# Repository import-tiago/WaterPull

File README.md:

# Water Pull
WaterPull is an electronic polymer dryer focused on removing moisture from 3D printer filaments. It has control and adjustment of temperature and curing time, internal air circulation and alarms.

## PCB Preview

## Enclosure Preview

## Schematic

### Contributing
0. Give this project a :star:
1. Create an issue and describe your idea.
2. [Fork it](https://github.com/import-tiago/WaterPull/fork).
3. Create your feature branch (`git checkout -b my-new-feature`).
4. Commit your changes (`git commit -a -m "Added feature title"`).
5. Publish the branch (`git push origin my-new-feature`).
6. Create a new pull request.
7. Done! :heavy_check_mark:

### License Information
<br /><span xmlns:dct="http://purl.org/dc/terms/" property="dct:title">ChristmasTree</span> by <a xmlns:cc="http://creativecommons.org/ns#" href="https://github.com/import-tiago" property="cc:attributionName" rel="cc:attributionURL">Tiago Silva</a> is licensed under a <a rel="license" href="http://creativecommons.org/licenses/by-sa/4.0/">Creative Commons Attribution-ShareAlike 4.0 International License</a>.<br />Permissions beyond the scope of this license may be available at <a xmlns:cc="http://creativecommons.org/ns#" href="https://twitter.com/import_tiago" rel="cc:morePermissions">tiagodepaulasilva@gmail.com</a>.

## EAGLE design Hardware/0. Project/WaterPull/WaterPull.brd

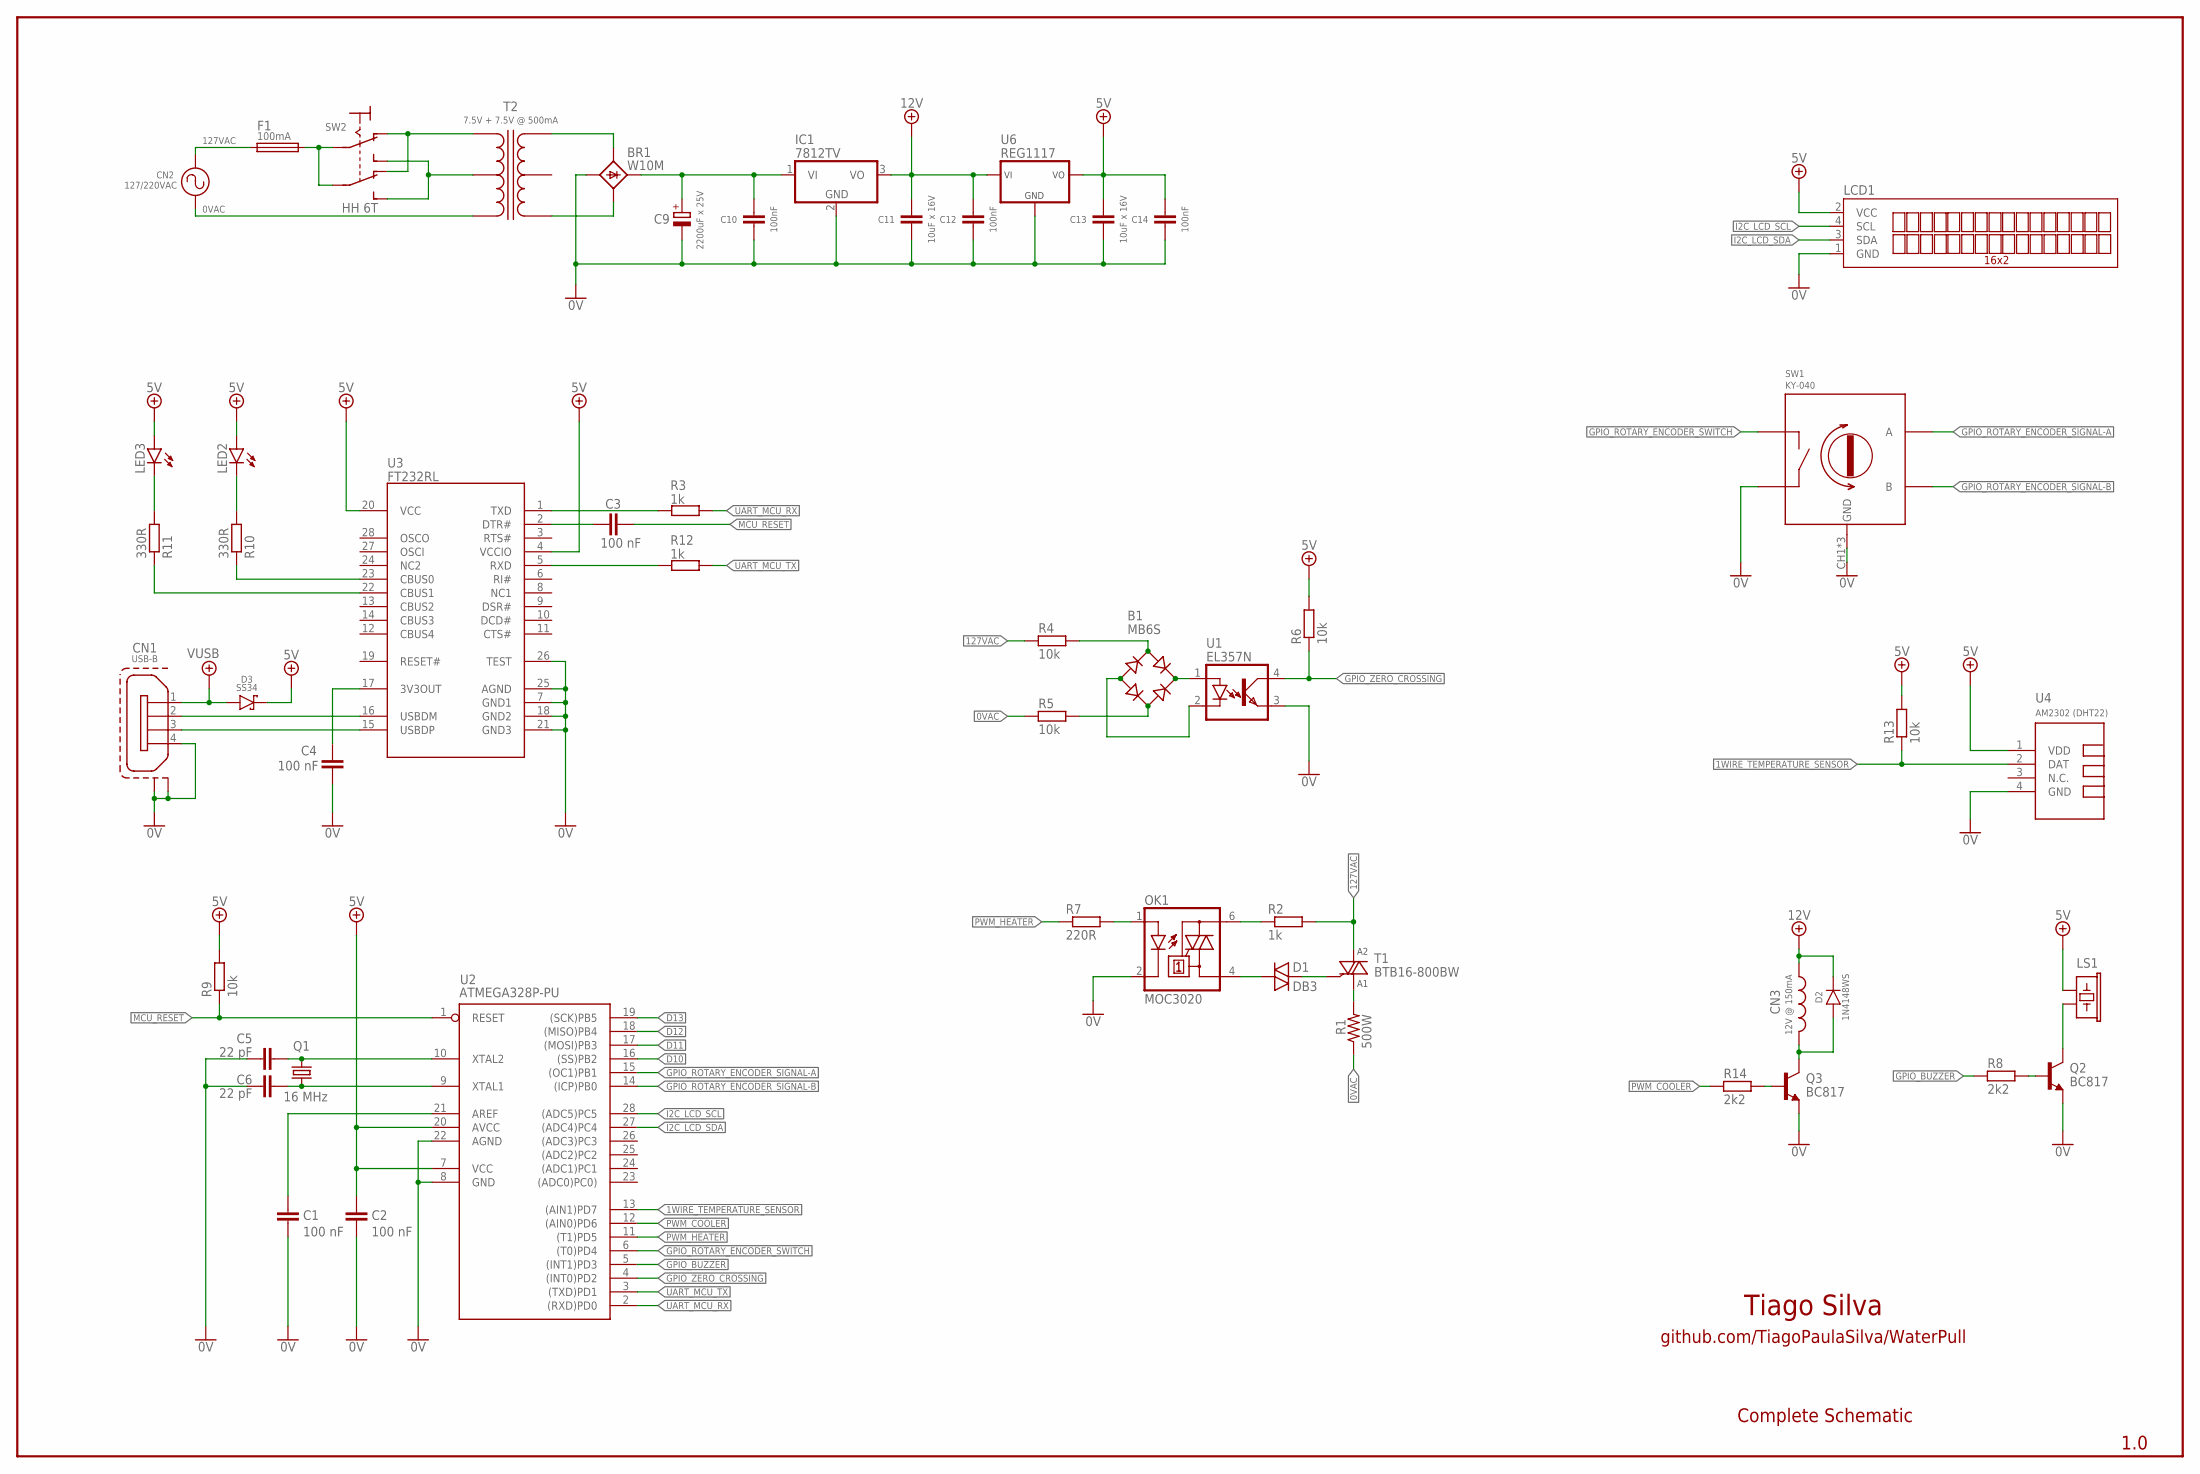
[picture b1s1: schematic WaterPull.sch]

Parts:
B1: MB6S; SOIC-4
BR1: W10M; DIOB_W005M
C1, C2, C3, C4: 100 nF; C0805
C5, C6: 22 pF; C0805
C9: 2200uF x 25V; E7,5-16
C10, C12, C14: 100nF; C0805
C11, C13: 10uF x 16V; C0805
CN1: USB-B
CN2: 127/220VAC; AK500/2-H
CN3: 12V @ 150mA; JST-PH2
D1: DB3; DO35-10
D2: 1N4148WS; SOD323F
D3: SS34; DO214AB
IC1: 7812TV; TO220V
LCD1: TUXGR_16X2_R2
LED2, LED3: LEDCHIPLED_0805; CHIPLED_0805
LS1: BUZZER-PTH; BUZZER-12MM
OK1: MOC3020; DIL06
Q1: 16 MHz; HC49/S
Q2, Q3: BC817; SOT23-BEC
R1: 500W; AK500/2-H
R2: 1k; 0207/7
R3, R12: 1k; R0805
R4, R5: 10k; 0207/7
R6, R9, R13: 10k; R0805
R7: 220R; R0805
R8, R14: 2k2; R0805
R10, R11: 330R; R0805
SW1: KY-040
T1: BTB16-800BW; TO220BH
T2: 7.5V + 7.5V @ 500mA; 3PINS
U1: EL357N; SOP254P700X200-4N
U2: ATMEGA328P-PU; DIL28-3
U3: FT232RL; SSOP28
U4: AM2302 (DHT22); TEMP-HUM-SENSOR-DHT22
U6: REG1117; SOT223

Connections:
0V: BR1.-, C1.2, C2.2, C4.1, C5.1, C6.1, C9.-, C10.2, C11.2, C12.2, C13.2, C14.2, CN1.4, CN1.M1 (S1), CN1.M2 (S2), IC1.2 (GND), LCD1.1 (GND), OK1.2 (C), Q2.E, Q3.E, SW1.CH1 (GND), SW1.CH2 (GND), SW1.GND, SW1.SW2, U1.3 (E), U2.8 (GND), U2.22 (AGND), U3.7 (GND1), U3.18 (GND2), U3.21 (GND3), U3.25 (AGND), U3.26 (TEST), U4.4 (GND), U6.1 (GND)
0VAC: CN2.1, R1.1, R5.1
1WIRE_TEMPERATURE_SENSOR: R13.1, U2.13 ((AIN1)PD7), U4.2 (DAT)
5V: C2.1, C13.1, C14.1, D3.C (K), LCD1.2 (VCC), LED2.A, LED3.A, LS1.+ (1), R6.2, R9.2, R13.2, U2.7 (VCC), U2.20 (AVCC), U3.4 (VCCIO), U3.20 (VCC), U4.1 (VDD), U6.2 (VOUT), U6.4 (VOUT)
12VDC: C11.1, C12.1, CN3.2 (1), D2.C (K), IC1.3 (VO), U6.3 (VIN)
127VAC: CN2.2, R2.2, R4.1, T1.T2 (A2)
A1: R1.2, T1.T1 (A1)
AREF: C1.1, U2.21 (AREF)
D10: U2.16 ((SS)PB2)
D11: U2.17 ((MOSI)PB3)
D12: U2.18 ((MISO)PB4)
D13: U2.19 ((SCK)PB5)
GND1: BR1.~B (AC2), T2.3
GPIO_BUZZER: R8.1, U2.5 ((INT1)PD3)
GPIO_ROTARY_ENCODER_SIGNAL-A: SW1.A, U2.15 ((OC1)PB1)
GPIO_ROTARY_ENCODER_SIGNAL-B: SW1.B, U2.14 ((ICP)PB0)
GPIO_ROTARY_ENCODER_SWITCH: SW1.SW1, U2.6 ((T0)PD4)
GPIO_ZERO_CROSSING: R6.1, U1.4 (C), U2.4 ((INT0)PD2)
I2C_LCD_SCL: LCD1.4 (SCL), U2.28 ((ADC5)PC5)
I2C_LCD_SDA: LCD1.3 (SDA), U2.27 ((ADC4)PC4)
MCU_RESET: C3.1, R9.1, U2.1 (RESET)
unnamed: D1.A (1), OK1.4 (A1)
unnamed: D1.C (2), T1.G
unnamed: B1.~1 (AC1), R4.2
unnamed: B1.~2 (AC2), R5.2
unnamed: B1.+, U1.1 (A)
unnamed: B1.-, U1.2 (K)
unnamed: R3.2, U3.1 (TXD)
unnamed: OK1.6 (A2), R2.1
unnamed: OK1.1 (A), R7.2
unnamed: LS1.- (2), Q2.C
unnamed: R12.2, U3.5 (RXD)
unnamed: BR1.+, C9.+, C10.1, IC1.1 (VI)
unnamed: C3.2, U3.2 (DTR#)
unnamed: R10.1, U3.23 (CBUS0)
unnamed: LED2.C, R10.2
unnamed: LED3.C, R11.2
unnamed: C5.2, Q1.2, U2.10 (XTAL2)
unnamed: C6.2, Q1.1, U2.9 (XTAL1)
unnamed: R11.1, U3.22 (CBUS1)
unnamed: C4.2, U3.17 (3V3OUT)
unnamed: CN1.2, U3.16 (USBDM)
unnamed: CN1.3, U3.15 (USBDP)
unnamed: Q2.B, R8.2
unnamed: CN3.1 (2), D2.A, Q3.C
unnamed: Q3.B, R14.2
unnamed: BR1.~A (AC1), T2.1
PWM_COOLER: R14.1, U2.12 ((AIN0)PD6)
PWM_HEATER: R7.1, U2.11 ((T1)PD5)
UART_MCU_RX: R3.1, U2.2 ((RXD)PD0)
UART_MCU_TX: R12.1, U2.3 ((TXD)PD1)
VUSB: CN1.1, D3.A

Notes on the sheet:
Tiago Silva
github.com/TiagoPaulaSilva/WaterPull
1.0
Complete Schematic

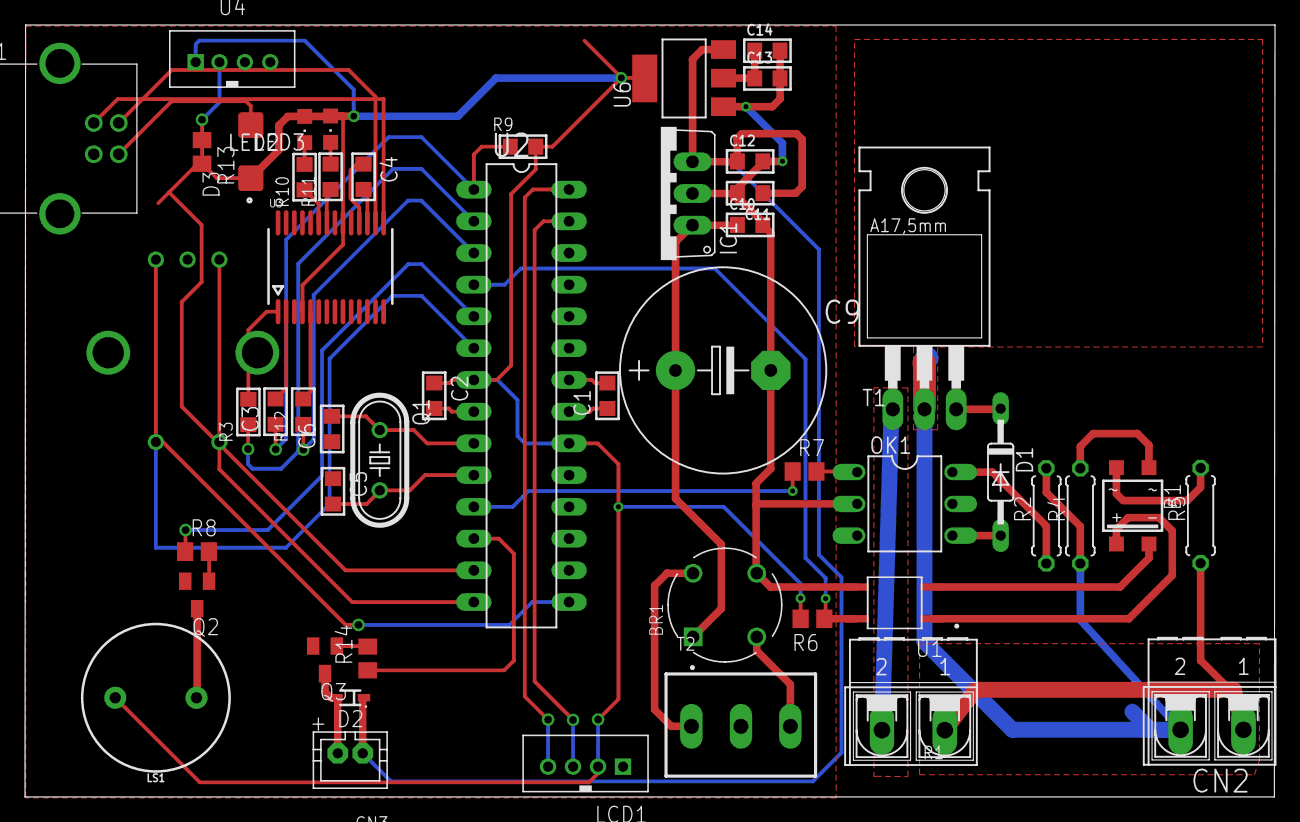
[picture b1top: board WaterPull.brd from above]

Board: 2 copper layers, 100.1 x 61.8 mm, 51 parts (1 on the bottom side), 48 nets.

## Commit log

2021-01-03 WIP PCB layout
2021-01-04 Schematic 1.0 - DONE
2021-01-04 Gerber files from schematic 1.0 generated
2021-01-04 Schematic 1.0 preview added
2021-01-04 Readme added
2021-01-04 PCB preview added
2021-01-04 Enclosure preview added
2021-01-04 Image resized
2021-01-22 Basic TRIAC test code
2023-07-21 usernames in URLs updated

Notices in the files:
parts and their libraries:
diy-modules: Released under the Creative Commons Attribution 4.0 International License: http://creativecommons.org/licenses/by/4.0
SparkFun-Electromechanical: Licensing: Creative Commons ShareAlike 4.0 International - https://creativecommons.org/licenses/by-sa/4.0
